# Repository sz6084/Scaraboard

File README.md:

# Scaraboard
A keyboard with some Scaramouche art on it!

### Inspiration

I wanted to create a keyboard to replace my old keyboard that I spilled a smoothie over, a (surprisingly decent and fully-sized) membrane keyboard. Scaraboard has 88 switches, 1 rpi pico, and no LEDs (I don't want the hassle and my current keyboard doesn't have it anyways, though RGB in a future one would be cool). Also Genshin Impact.

### Challenge

I had only just designed my macropad, and now i had to scale it up. I followed an online guide and consulted my trusty friend who had more experience than I did. I also asked questions in the Hack Club Slack.

### Specifications

## Bill of Material
| Part | Qty | Price | Link |
| --- | --- | --- | --- |
| PCB | 5 | $21.50 | https://cart.jlcpcb.com/quote?orderType=1&homeUploadNum=f9d340d1b5944b91bde815b77c3f36ea&businessType=example&fileName=hackboard.zip |
| MX Switches | 88 | $17.60 | https://mechanicalkeyboards.com/products/gateron-ks-3-milky-yellow-pro-50g-linear-pcb-mount |
| Keycaps | 88 | $13.99 | https://www.amazon.com/Doubleshot-Mechanical-Keyboard-Compatiability-Keyboads/dp/B0F7H32LKC |
| Stabilizers | 1 | $10.00 | https://cannonkeys.com/products/cherry-stabilizers?variant=32257338998895 |
| 1N4148 Diode | 88 | $8.80 | https://www.digikey.com/en/products/detail/onsemi/1N4148/458603 |
| Orpheus Pi Pico | 2 | --- | https://orpheuspico.hackclub.com |
| Subtotal | --- | $77.89 | --- |
| Approx. Total Price (with shipping) | --- | $106.33 | --- |

Others:
 - Case is 3d printed in PLA
 - 4x M3x12 screw
 - 4x M3x4 heat set inserts
 - KMK firmware

Schematic            |  PCB         |   Case
:-------------------------:|:-------------------------:|:-------------------------:|
|  |   |   |

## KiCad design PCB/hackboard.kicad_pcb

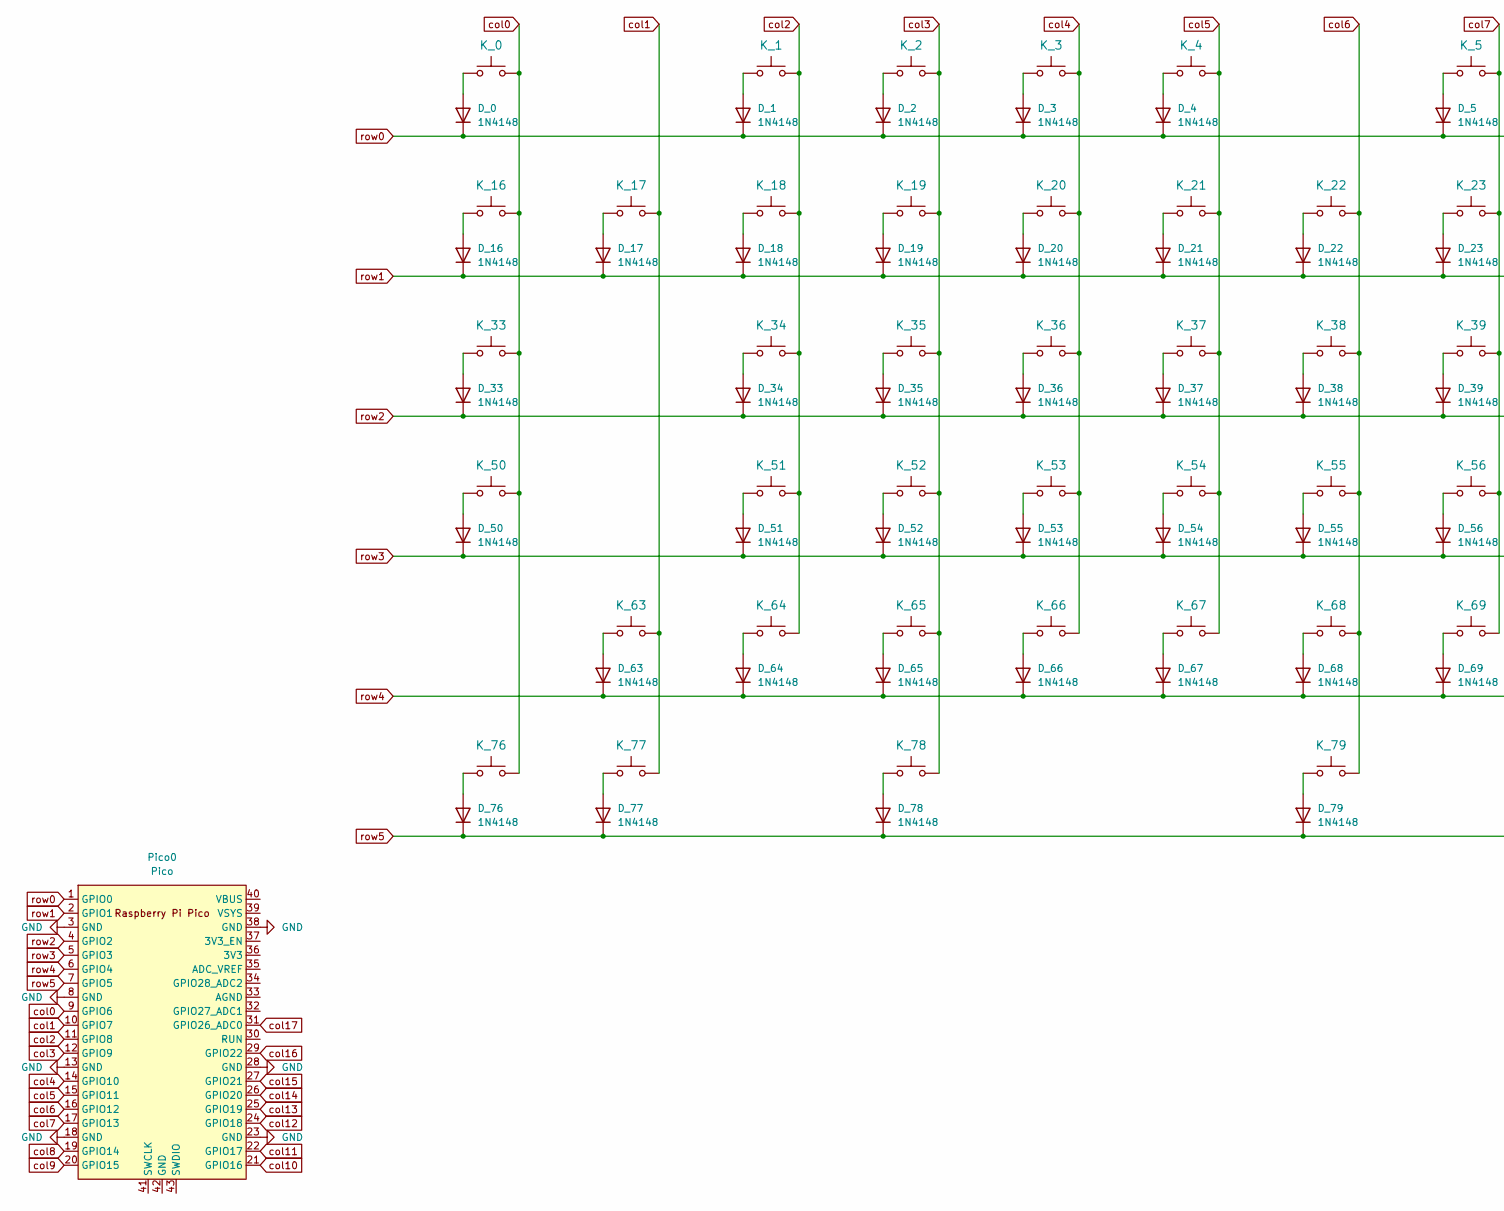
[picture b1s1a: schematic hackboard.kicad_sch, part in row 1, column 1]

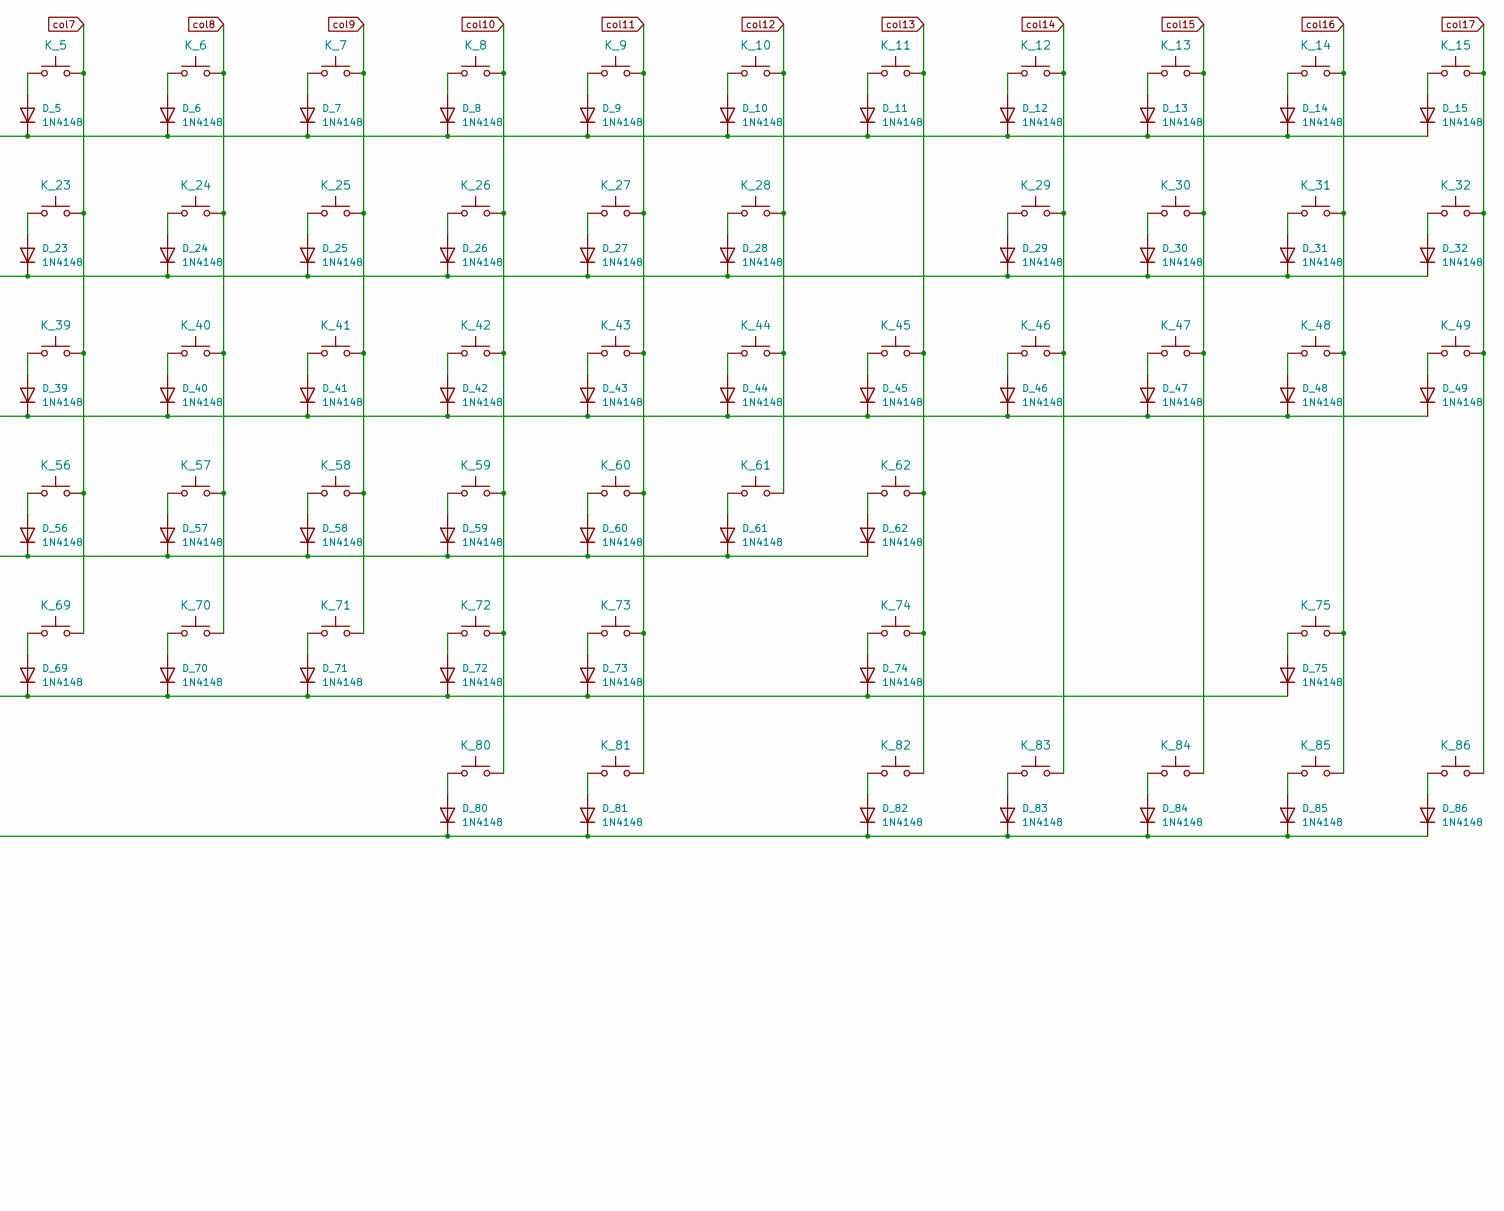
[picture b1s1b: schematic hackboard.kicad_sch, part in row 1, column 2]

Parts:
D_0, D_1, D_2, D_3, D_4, D_5, D_6, D_7, D_8, D_9, D_10, D_11, D_12, D_13, D_14, D_15, D_16, D_17, D_18, D_19, D_20, D_21, D_22, D_23, D_24, D_25, D_26, D_27, D_28, D_29, D_30, D_31, D_32, D_33, D_34, D_35, D_36, D_37, D_38, D_39, D_40, D_41, D_42, D_43, D_44, D_45, D_46, D_47, D_48, D_49, D_50, D_51, D_52, D_53, D_54, D_55, D_56, D_57, D_58, D_59, D_60, D_61, D_62, D_63, D_64, D_65, D_66, D_67, D_68, D_69, D_70, D_71, D_72, D_73, D_74, D_75, D_76, D_77, D_78, D_79, D_80, D_81, D_82, D_83, D_84, D_85, D_86: 1N4148; D_DO-35_SOD27_P7.62mm_Horizontal
K_0, K_1, K_2, K_3, K_4, K_5, K_6, K_7, K_8, K_9, K_10, K_11, K_12, K_13, K_14, K_15, K_16, K_17, K_18, K_19, K_20, K_21, K_22, K_23, K_24, K_25, K_26, K_27, K_28, K_30, K_31, K_32, K_34, K_35, K_36, K_37, K_38, K_39, K_40, K_41, K_42, K_43, K_44, K_45, K_47, K_48, K_49, K_51, K_52, K_53, K_54, K_55, K_56, K_57, K_58, K_59, K_60, K_61, K_64, K_65, K_66, K_67, K_68, K_69, K_70, K_71, K_72, K_73, K_75, K_84, K_85, K_86: KEYSW; SW_Cherry_MX_1.00u_PCB
K_29: KEYSW; SW_Cherry_MX_2.00u_PCB
K_33, K_46: KEYSW; SW_Cherry_MX_1.50u_PCB
K_50: KEYSW; SW_Cherry_MX_1.75u_PCB
K_62, K_63: KEYSW; SW_Cherry_MX_2.25u_PCB
K_74: KEYSW; SW_Cherry_MX_2.75u_PCB
K_76, K_77, K_78, K_80, K_81, K_82, K_83: KEYSW; SW_Cherry_MX_1.25u_PCB
K_79: KEYSW; SW_Cherry_MX_6.25u_PCB
Pico0: Pico; RPi_Pico_SMD_TH

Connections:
GND: Pico0.3 (GND), Pico0.8 (GND), Pico0.13 (GND), Pico0.18 (GND), Pico0.23 (GND), Pico0.28 (GND), Pico0.38 (GND)
unnamed: D_0.2 (A), K_0.1
unnamed: D_1.2 (A), K_1.1
unnamed: D_2.2 (A), K_2.1
unnamed: D_3.2 (A), K_3.1
unnamed: D_4.2 (A), K_4.1
unnamed: D_5.2 (A), K_5.1
unnamed: D_6.2 (A), K_6.1
unnamed: D_7.2 (A), K_7.1
unnamed: D_8.2 (A), K_8.1
unnamed: D_9.2 (A), K_9.1
unnamed: D_10.2 (A), K_10.1
unnamed: D_11.2 (A), K_11.1
unnamed: D_12.2 (A), K_12.1
unnamed: D_13.2 (A), K_13.1
unnamed: D_14.2 (A), K_14.1
unnamed: D_15.2 (A), K_15.1
unnamed: D_16.2 (A), K_16.1
unnamed: D_17.2 (A), K_17.1
unnamed: D_18.2 (A), K_18.1
unnamed: D_19.2 (A), K_19.1
unnamed: D_20.2 (A), K_20.1
unnamed: D_21.2 (A), K_21.1
unnamed: D_22.2 (A), K_22.1
unnamed: D_23.2 (A), K_23.1
unnamed: D_24.2 (A), K_24.1
unnamed: D_25.2 (A), K_25.1
unnamed: D_26.2 (A), K_26.1
unnamed: D_27.2 (A), K_27.1
unnamed: D_28.2 (A), K_28.1
unnamed: D_29.2 (A), K_29.1
unnamed: D_30.2 (A), K_30.1
unnamed: D_31.2 (A), K_31.1
unnamed: D_32.2 (A), K_32.1
unnamed: D_33.2 (A), K_33.1
unnamed: D_34.2 (A), K_34.1
unnamed: D_35.2 (A), K_35.1
unnamed: D_36.2 (A), K_36.1
unnamed: D_37.2 (A), K_37.1
unnamed: D_38.2 (A), K_38.1
unnamed: D_39.2 (A), K_39.1
unnamed: D_40.2 (A), K_40.1
unnamed: D_41.2 (A), K_41.1
unnamed: D_42.2 (A), K_42.1
unnamed: D_43.2 (A), K_43.1
unnamed: D_44.2 (A), K_44.1
unnamed: D_45.2 (A), K_45.1
unnamed: D_46.2 (A), K_46.1
unnamed: D_47.2 (A), K_47.1
unnamed: D_48.2 (A), K_48.1
unnamed: D_49.2 (A), K_49.1
unnamed: D_50.2 (A), K_50.1
unnamed: D_51.2 (A), K_51.1
unnamed: D_52.2 (A), K_52.1
unnamed: D_53.2 (A), K_53.1
unnamed: D_54.2 (A), K_54.1
unnamed: D_55.2 (A), K_55.1
unnamed: D_56.2 (A), K_56.1
unnamed: D_57.2 (A), K_57.1
unnamed: D_58.2 (A), K_58.1
unnamed: D_59.2 (A), K_59.1
unnamed: D_60.2 (A), K_60.1
unnamed: D_61.2 (A), K_61.1
unnamed: D_62.2 (A), K_62.1
unnamed: D_63.2 (A), K_63.1
unnamed: D_64.2 (A), K_64.1
unnamed: D_65.2 (A), K_65.1
unnamed: D_66.2 (A), K_66.1
unnamed: D_67.2 (A), K_67.1
unnamed: D_68.2 (A), K_68.1
unnamed: D_69.2 (A), K_69.1
unnamed: D_70.2 (A), K_70.1
unnamed: D_71.2 (A), K_71.1
unnamed: D_72.2 (A), K_72.1
unnamed: D_73.2 (A), K_73.1
unnamed: D_74.2 (A), K_74.1
unnamed: D_75.2 (A), K_75.1
unnamed: D_76.2 (A), K_76.1
unnamed: D_77.2 (A), K_77.1
unnamed: D_78.2 (A), K_78.1
unnamed: D_79.2 (A), K_79.1
unnamed: D_80.2 (A), K_80.1
unnamed: D_81.2 (A), K_81.1
unnamed: D_82.2 (A), K_82.1
unnamed: D_83.2 (A), K_83.1
unnamed: D_84.2 (A), K_84.1
unnamed: D_85.2 (A), K_85.1
unnamed: D_86.2 (A), K_86.1
col0: K_0.2, K_16.2, K_33.2, K_50.2, K_76.2, Pico0.9 (GPIO6)
col1: K_17.2, K_63.2, K_77.2, Pico0.10 (GPIO7)
col2: K_1.2, K_18.2, K_34.2, K_51.2, K_64.2, Pico0.11 (GPIO8)
col3: K_2.2, K_19.2, K_35.2, K_52.2, K_65.2, K_78.2, Pico0.12 (GPIO9)
col4: K_3.2, K_20.2, K_36.2, K_53.2, K_66.2, Pico0.14 (GPIO10)
col5: K_4.2, K_21.2, K_37.2, K_54.2, K_67.2, Pico0.15 (GPIO11)
col6: K_22.2, K_38.2, K_55.2, K_68.2, K_79.2, Pico0.16 (GPIO12)
col7: K_5.2, K_23.2, K_39.2, K_56.2, K_69.2, Pico0.17 (GPIO13)
col8: K_6.2, K_24.2, K_40.2, K_57.2, K_70.2, Pico0.19 (GPIO14)
col9: K_7.2, K_25.2, K_41.2, K_58.2, K_71.2, Pico0.20 (GPIO15)
col10: K_8.2, K_26.2, K_42.2, K_59.2, K_72.2, K_80.2, Pico0.21 (GPIO16)
col11: K_9.2, K_27.2, K_43.2, K_60.2, K_73.2, K_81.2, Pico0.22 (GPIO17)
col12: K_10.2, K_28.2, K_44.2, K_61.2, Pico0.24 (GPIO18)
col13: K_11.2, K_45.2, K_62.2, K_74.2, K_82.2, Pico0.25 (GPIO19)
col14: K_12.2, K_29.2, K_46.2, K_83.2, Pico0.26 (GPIO20)
col15: K_13.2, K_30.2, K_47.2, K_84.2, Pico0.27 (GPIO21)
col16: K_14.2, K_31.2, K_48.2, K_75.2, K_85.2, Pico0.29 (GPIO22)
col17: K_15.2, K_32.2, K_49.2, K_86.2, Pico0.31 (GPIO26_ADC0)
row0: D_0.1 (K), D_1.1 (K), D_2.1 (K), D_3.1 (K), D_4.1 (K), D_5.1 (K), D_6.1 (K), D_7.1 (K), D_8.1 (K), D_9.1 (K), D_10.1 (K), D_11.1 (K), D_12.1 (K), D_13.1 (K), D_14.1 (K), D_15.1 (K), Pico0.1 (GPIO0)
row1: D_16.1 (K), D_17.1 (K), D_18.1 (K), D_19.1 (K), D_20.1 (K), D_21.1 (K), D_22.1 (K), D_23.1 (K), D_24.1 (K), D_25.1 (K), D_26.1 (K), D_27.1 (K), D_28.1 (K), D_29.1 (K), D_30.1 (K), D_31.1 (K), D_32.1 (K), Pico0.2 (GPIO1)
row2: D_33.1 (K), D_34.1 (K), D_35.1 (K), D_36.1 (K), D_37.1 (K), D_38.1 (K), D_39.1 (K), D_40.1 (K), D_41.1 (K), D_42.1 (K), D_43.1 (K), D_44.1 (K), D_45.1 (K), D_46.1 (K), D_47.1 (K), D_48.1 (K), D_49.1 (K), Pico0.4 (GPIO2)
row3: D_50.1 (K), D_51.1 (K), D_52.1 (K), D_53.1 (K), D_54.1 (K), D_55.1 (K), D_56.1 (K), D_57.1 (K), D_58.1 (K), D_59.1 (K), D_60.1 (K), D_61.1 (K), D_62.1 (K), Pico0.5 (GPIO3)
row4: D_63.1 (K), D_64.1 (K), D_65.1 (K), D_66.1 (K), D_67.1 (K), D_68.1 (K), D_69.1 (K), D_70.1 (K), D_71.1 (K), D_72.1 (K), D_73.1 (K), D_74.1 (K), D_75.1 (K), Pico0.6 (GPIO4)
row5: D_76.1 (K), D_77.1 (K), D_78.1 (K), D_79.1 (K), D_80.1 (K), D_81.1 (K), D_82.1 (K), D_83.1 (K), D_84.1 (K), D_85.1 (K), D_86.1 (K), Pico0.7 (GPIO5)

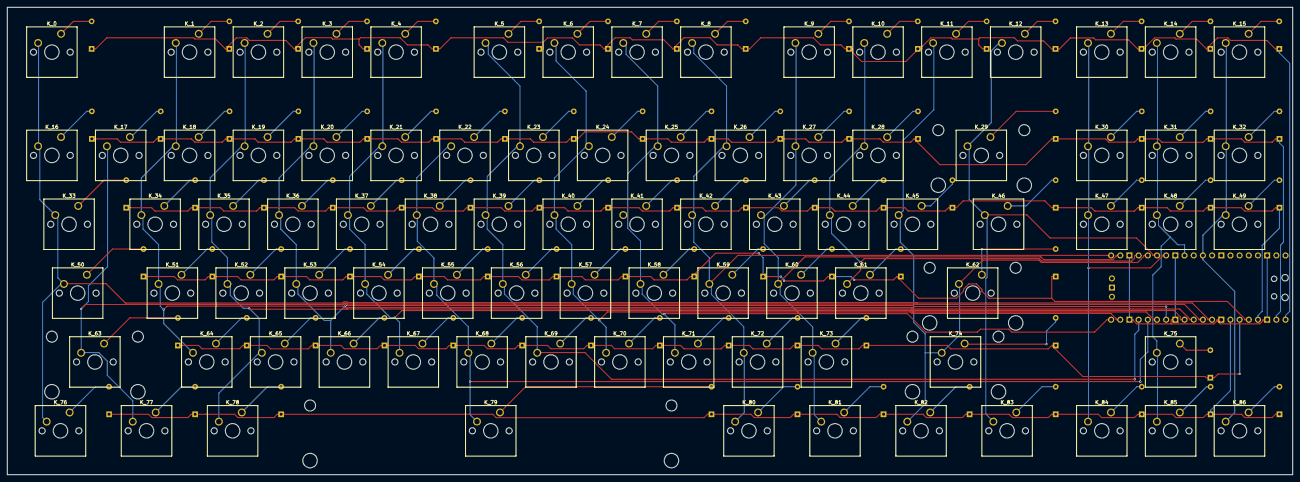
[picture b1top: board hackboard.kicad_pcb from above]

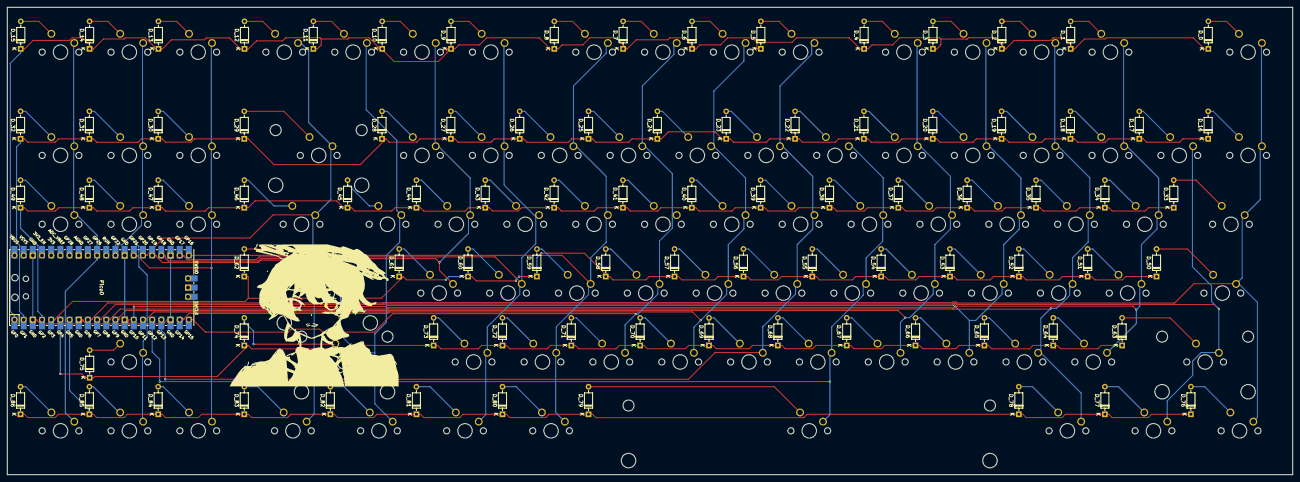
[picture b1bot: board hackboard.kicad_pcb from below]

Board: 2 copper layers, 355.7 x 129.3 mm, 175 parts (88 on the bottom side), 112 nets.

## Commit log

2025-03-10 Initialized KiCAD project
2025-03-14 Added KiCad-RP-PICO submodule to the project.
2025-03-14 Initialized keyboard using auto-generated layout tool and added a 3D Model
2025-03-15 Moved MCB
2025-03-15 Finished Routing
2025-03-15 Moved diodes
2025-03-16 Updated symbols and routing
2025-03-17 Removed unused row
2025-03-23 Changed silkscreen art
2025-03-25 Added a temporary firmware program
2025-03-25 Preliminary README
2025-03-31 Added missing key in keymap
2025-10-07 Add BOM.csv
2025-10-07 Uploaded CAD file
2025-10-07 Update README.md
    Added PCB to BOM
2025-10-07 Added BOM.csv as an exception to .gitignore
2025-10-07 modified: .gitignore
2025-10-08 Update README.md
    Added Keycaps and Stabilizers to BOM as well as a Subtotal Row. Updated Total Price
2025-10-08 Update BOM.csv
    Updated to align with the BOM in the README.MD
2025-10-08 Update README.md
    Updated keycap URL/price to a better one
2025-10-08 Update README.md
    Updated Subtotal
2025-10-09 Moved production folder and added STLs and copy of firmware to it
2025-10-13 Update README.md
    Changed MCU from Raspberry to Orpheus
2025-10-13 Update BOM.csv
    Changed MCU from Raspberry Pi Pico to Orpheus
